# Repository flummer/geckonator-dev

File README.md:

# Geckonator Dev Edition

This is a follow-up version og the [original Geckonator hardware][geckonator-hw] and is, similarly to the original, designed to help in early design work with the Silabs Happy Gecko family of USB microsontrollers.

This board, compared to the original, has two buttons (one to enter bootloader mode and one for power), a larger chip with more pins, all broken out, 3 LED's instead of 2, and a large prototyping area, where other stuff can be soldered on to for a semi permanent setup.

[geckonator-hw]: https://github.com/flummer/geckonator-hw

## Firmware

This board is designed for the development of the [Geckoboot bootloader][geckoboot], and for developing applications for this, the [Geckonator][geckonator] repository can be used as a base

[geckoboot]: https://github.com/flummer/geckoboot
[geckonator]: https://github.com/flummer/geckonator

## Hardware

This design is using the [Seeed OPL for KiCad library][seeed-opl] for all components, except for the EMF32 microcontroller. They are all standard components and can easily be replaced with parts sourced from other places.

[seeed-opl]: https://github.com/Seeed-Studio/OPL_Kicad_Library

## License

The contents of this repository is released under the following licence:

 * the "Creative Commons Attribution-ShareAlike 4.0 International License"
   (CC BY-SA 4.0) full text of this license is included in the LICENSE file
   and a copy can also be found at
   http://creativecommons.org/licenses/by-sa/4.0/

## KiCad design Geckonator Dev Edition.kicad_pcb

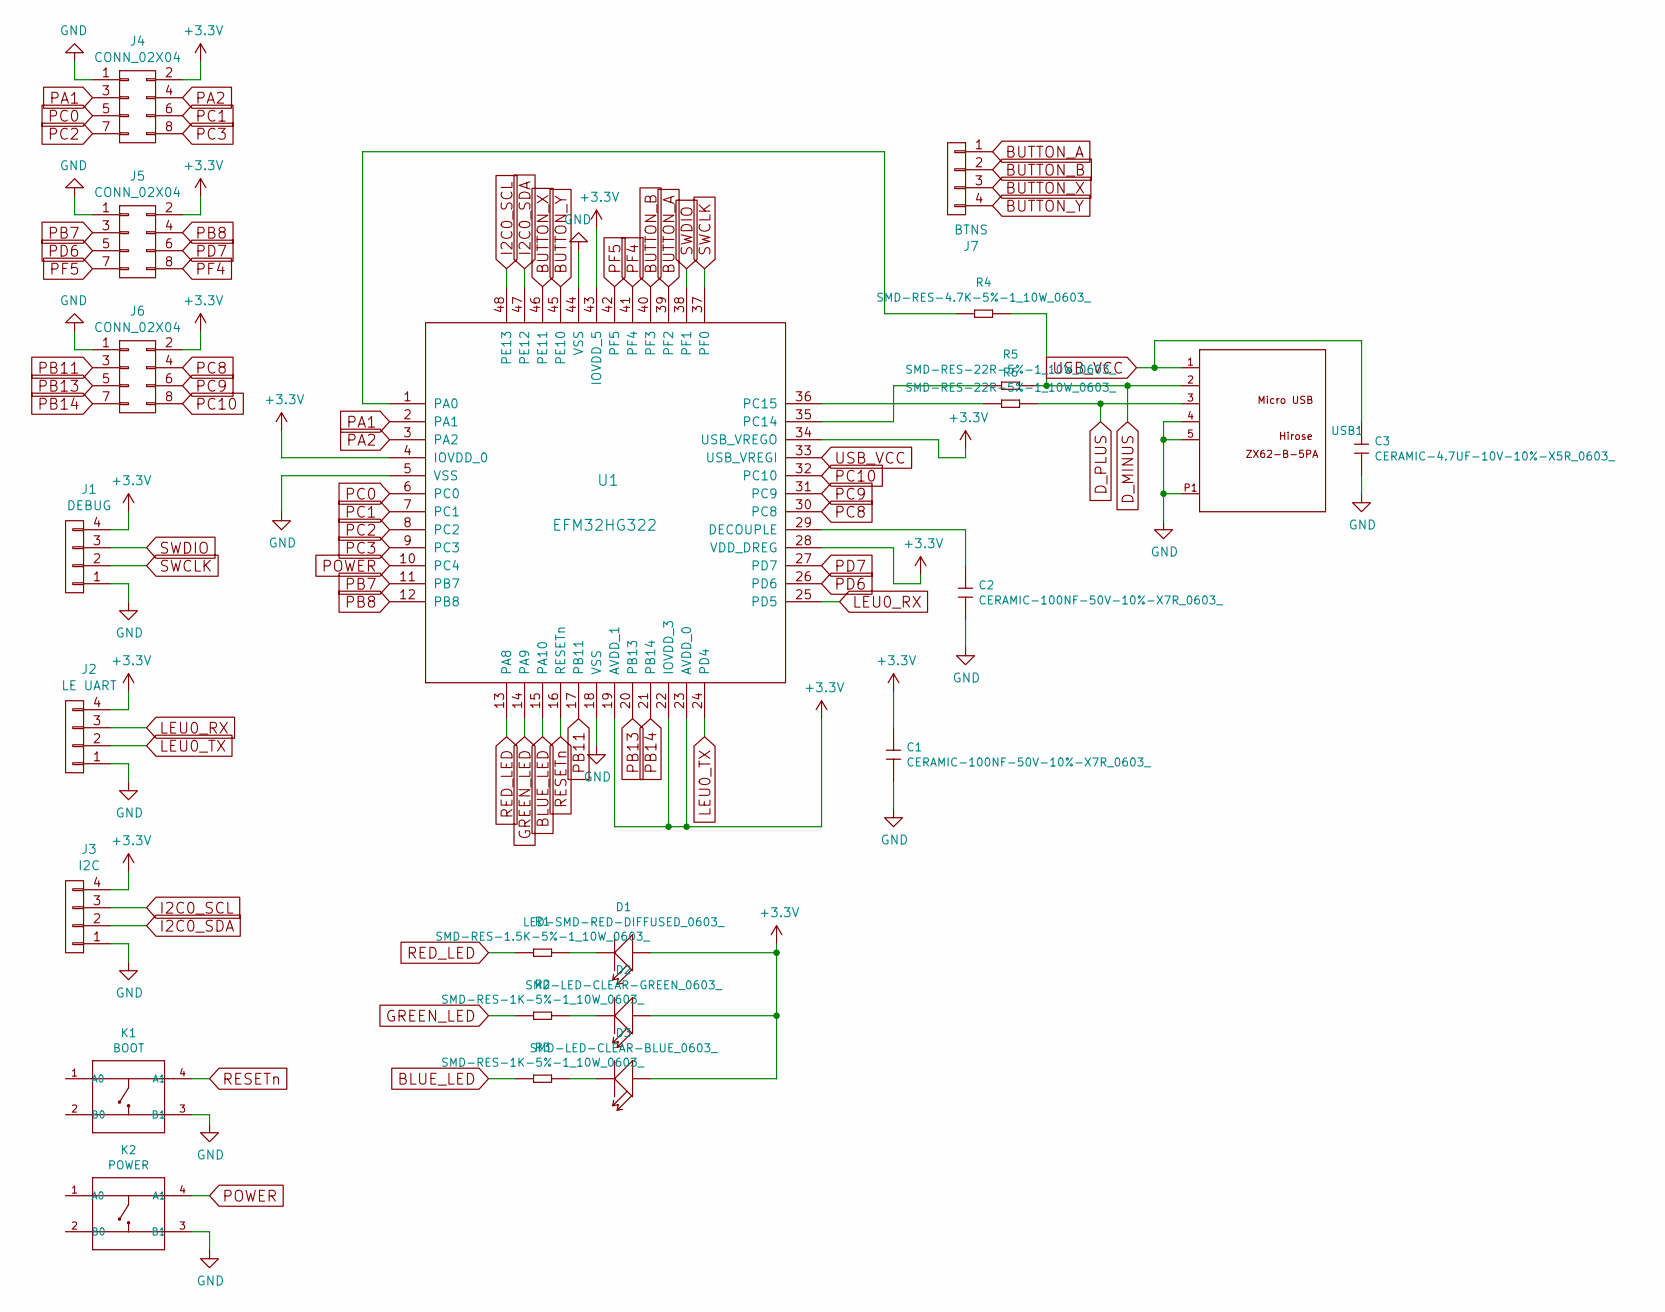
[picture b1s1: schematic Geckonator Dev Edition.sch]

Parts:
C1, C2: CERAMIC-100NF-50V-10%-X7R_0603_; C0603; MPN CC0603KRX7R9BB104
C3: CERAMIC-4.7UF-10V-10%-X5R_0603_; C0603; MPN CC0603KRX5R6BB475
D1: LED-SMD-RED-DIFFUSED_0603_; LED-0603; MPN 19-217-R6C-AL1M2VY-3T
D2: SMD-LED-CLEAR-GREEN_0603_; LED-0603; MPN 19-217-G7C-AN1P2-3T
D3: SMD-LED-CLEAR-BLUE_0603_; LED-0603; MPN 19-217-BHC-ZL1M2RY-3T
J1: DEBUG; Pin_Header_Straight_1x04_Pitch2.54mm
J2: LE UART; Pin_Header_Straight_1x04_Pitch2.54mm
J3: I2C; Pin_Header_Straight_1x04_Pitch2.54mm
J4, J5, J6: CONN_02X04; Pin_Header_Straight_2x04_Pitch2.54mm
J7: BTNS; Pin_Header_Straight_1x04_Pitch2.54mm
K1: BOOT; SW4-SMD-6.0X6.0X5.0MM; MPN DTSM-62K-S-V-T_R_SN431_
K2: POWER; SW4-SMD-6.0X6.0X5.0MM; MPN DTSM-62K-S-V-T_R_SN431_
R1: SMD-RES-1.5K-5%-1_10W_0603_; R0603; MPN RC0603JR-071K5L
R2, R3: SMD-RES-1K-5%-1_10W_0603_; R0603; MPN RC0603JR-071KL
R4: SMD-RES-4.7K-5%-1_10W_0603_; R0603; MPN RC0603JR-074K7L
R5, R6: SMD-RES-22R-5%-1_10W_0603_; R0603; MPN RC0603JR-0722RL
U1: EFM32HG322; TQFP-48_7x7mm_Pitch0.5mm
USB1: MICRO-USB-SMD_ZX62-B-5PA_; MICRO-USB5+6P-SMD-0.65-AB; MPN ZX62-B-5PA

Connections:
+3V3: C1.1, D1.+, D2.+, D3.+, J1.4, J2.4, J3.4, J4.2, J5.2, J6.2, U1.4 (IOVDD_0), U1.19 (AVDD_1), U1.22 (IOVDD_3), U1.23 (AVDD_0), U1.28 (VDD_DREG), U1.34 (USB_VREGO), U1.43 (IOVDD_5)
BLUE_LED: R3.1, U1.15 (PA10)
BUTTON_A: J7.1, U1.39 (PF2)
BUTTON_B: J7.2, U1.40 (PF3)
BUTTON_X: J7.3, U1.46 (PE11)
BUTTON_Y: J7.4, U1.45 (PE10)
D_MINUS: R4.2, R5.2, USB1.2 (D-)
D_PLUS: R6.2, USB1.3 (D+)
GND: C1.2, C2.2, C3.2, J1.1, J2.1, J3.1, J4.1, J5.1, J6.1, K1.3 (B1), K2.3 (B1), U1.5 (VSS), U1.18 (VSS), U1.44 (VSS), USB1.4 (ID), USB1.5 (GND), USB1.P1 (SHIELD), USB1.P2 (SHIELD), USB1.P3 (SHIELD), USB1.P4 (SHIELD), USB1.P5 (SHIELD), USB1.P6 (SHIELD)
GREEN_LED: R2.1, U1.14 (PA9)
I2C0_SCL: J3.3, U1.48 (PE13)
I2C0_SDA: J3.2, U1.47 (PE12)
LEU0_RX: J2.3, U1.25 (PD5)
LEU0_TX: J2.2, U1.24 (PD4)
unnamed: C2.1, U1.29 (DECOUPLE)
unnamed: D1.-, R1.2
unnamed: D2.-, R2.2
unnamed: D3.-, R3.2
unnamed: R4.1, U1.1 (PA0)
unnamed: R5.1, U1.35 (PC14)
unnamed: R6.1, U1.36 (PC15)
PA1: J4.3, U1.2 (PA1)
PA2: J4.4, U1.3 (PA2)
PB7: J5.3, U1.11 (PB7)
PB8: J5.4, U1.12 (PB8)
PB11: J6.3, U1.17 (PB11)
PB13: J6.5, U1.20 (PB13)
PB14: J6.7, U1.21 (PB14)
PC0: J4.5, U1.6 (PC0)
PC1: J4.6, U1.7 (PC1)
PC2: J4.7, U1.8 (PC2)
PC3: J4.8, U1.9 (PC3)
PC8: J6.4, U1.30 (PC8)
PC9: J6.6, U1.31 (PC9)
PC10: J6.8, U1.32 (PC10)
PD6: J5.5, U1.26 (PD6)
PD7: J5.6, U1.27 (PD7)
PF4: J5.8, U1.41 (PF4)
PF5: J5.7, U1.42 (PF5)
POWER: K2.4 (A1), U1.10 (PC4)
RED_LED: R1.1, U1.13 (PA8)
RESETn: K1.4 (A1), U1.16 (RESETn)
SWCLK: J1.2, U1.37 (PF0)
SWDIO: J1.3, U1.38 (PF1)
USB_VCC: C3.1, U1.33 (USB_VREGI), USB1.1 (VBUS)

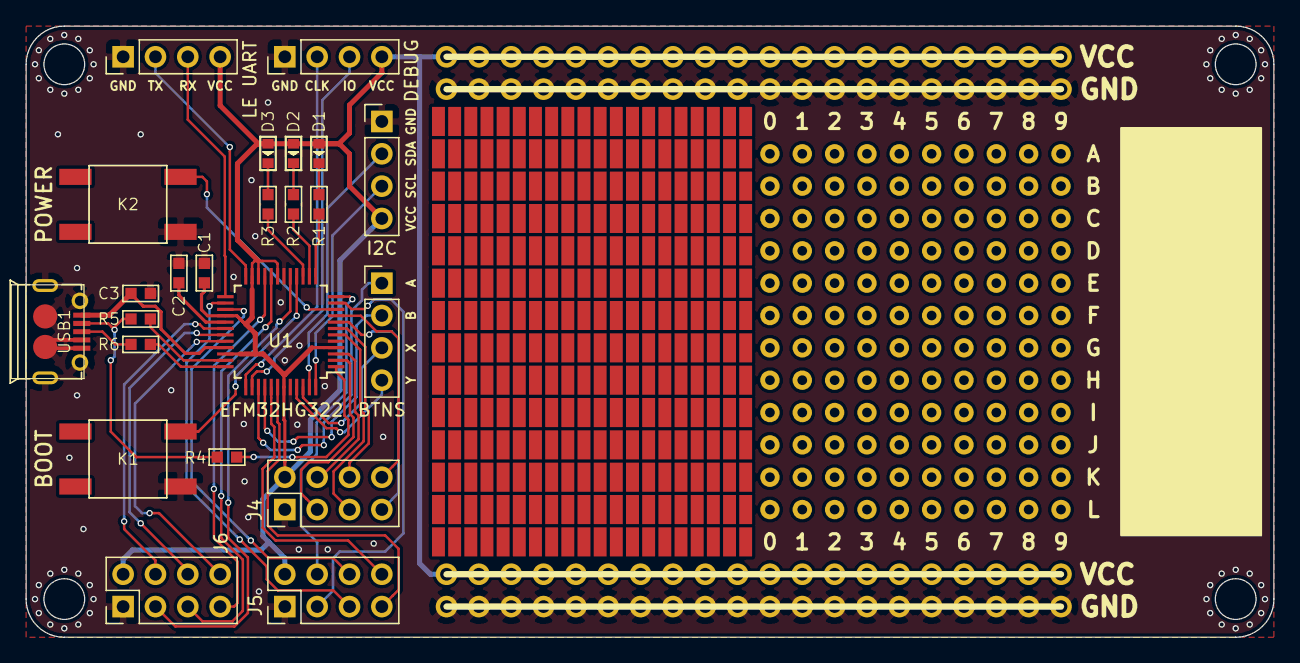
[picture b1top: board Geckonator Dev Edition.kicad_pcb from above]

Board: 2 copper layers, 98.0 x 48.0 mm, 23 parts (0 on the bottom side), 45 nets.

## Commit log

2018-03-18 Initial version
    Only schematics
2018-04-25 Added silkscreen, etc.
    This corresponds to the first version produced
2018-04-25 Added gerber files
    Also added .gitignore
2018-12-09 Added readme.md information
2018-12-09 Added PDF schematic, licensing info and efm32 lib
2018-12-10 Added info about Seeed OPL library
